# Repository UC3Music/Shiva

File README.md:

Shiva
--------------------------
Up to 8 piezo sensors with MIDI out (standard and USB) to make an electronic drumset

## v1.0 Prototype
### Known bugs

[Known bugs](https://github.com/UC3Music/Shiva/issues?q=is%3Aissue+is%3Aopen+label%3Abug)

## v0.1 Prototype
### PCBs

## Proof of concept

Proof of concept done with an Arduino Micro board (click on the images below to go to the videos):

# Acknowledgments

 * Inspired by KORG's [CLIPHIT](http://www.korg.com/us/products/drums/cliphit/)
 * Conditioning circuit for piezo sensors is based on [ScienceProg's circuit](http://www.scienceprog.com/thoughts-on-interfacing-piezo-vibration-sensor/)

# Credits
* Author: [David Estevez Fernandez](https://github.com/David-Estevez)

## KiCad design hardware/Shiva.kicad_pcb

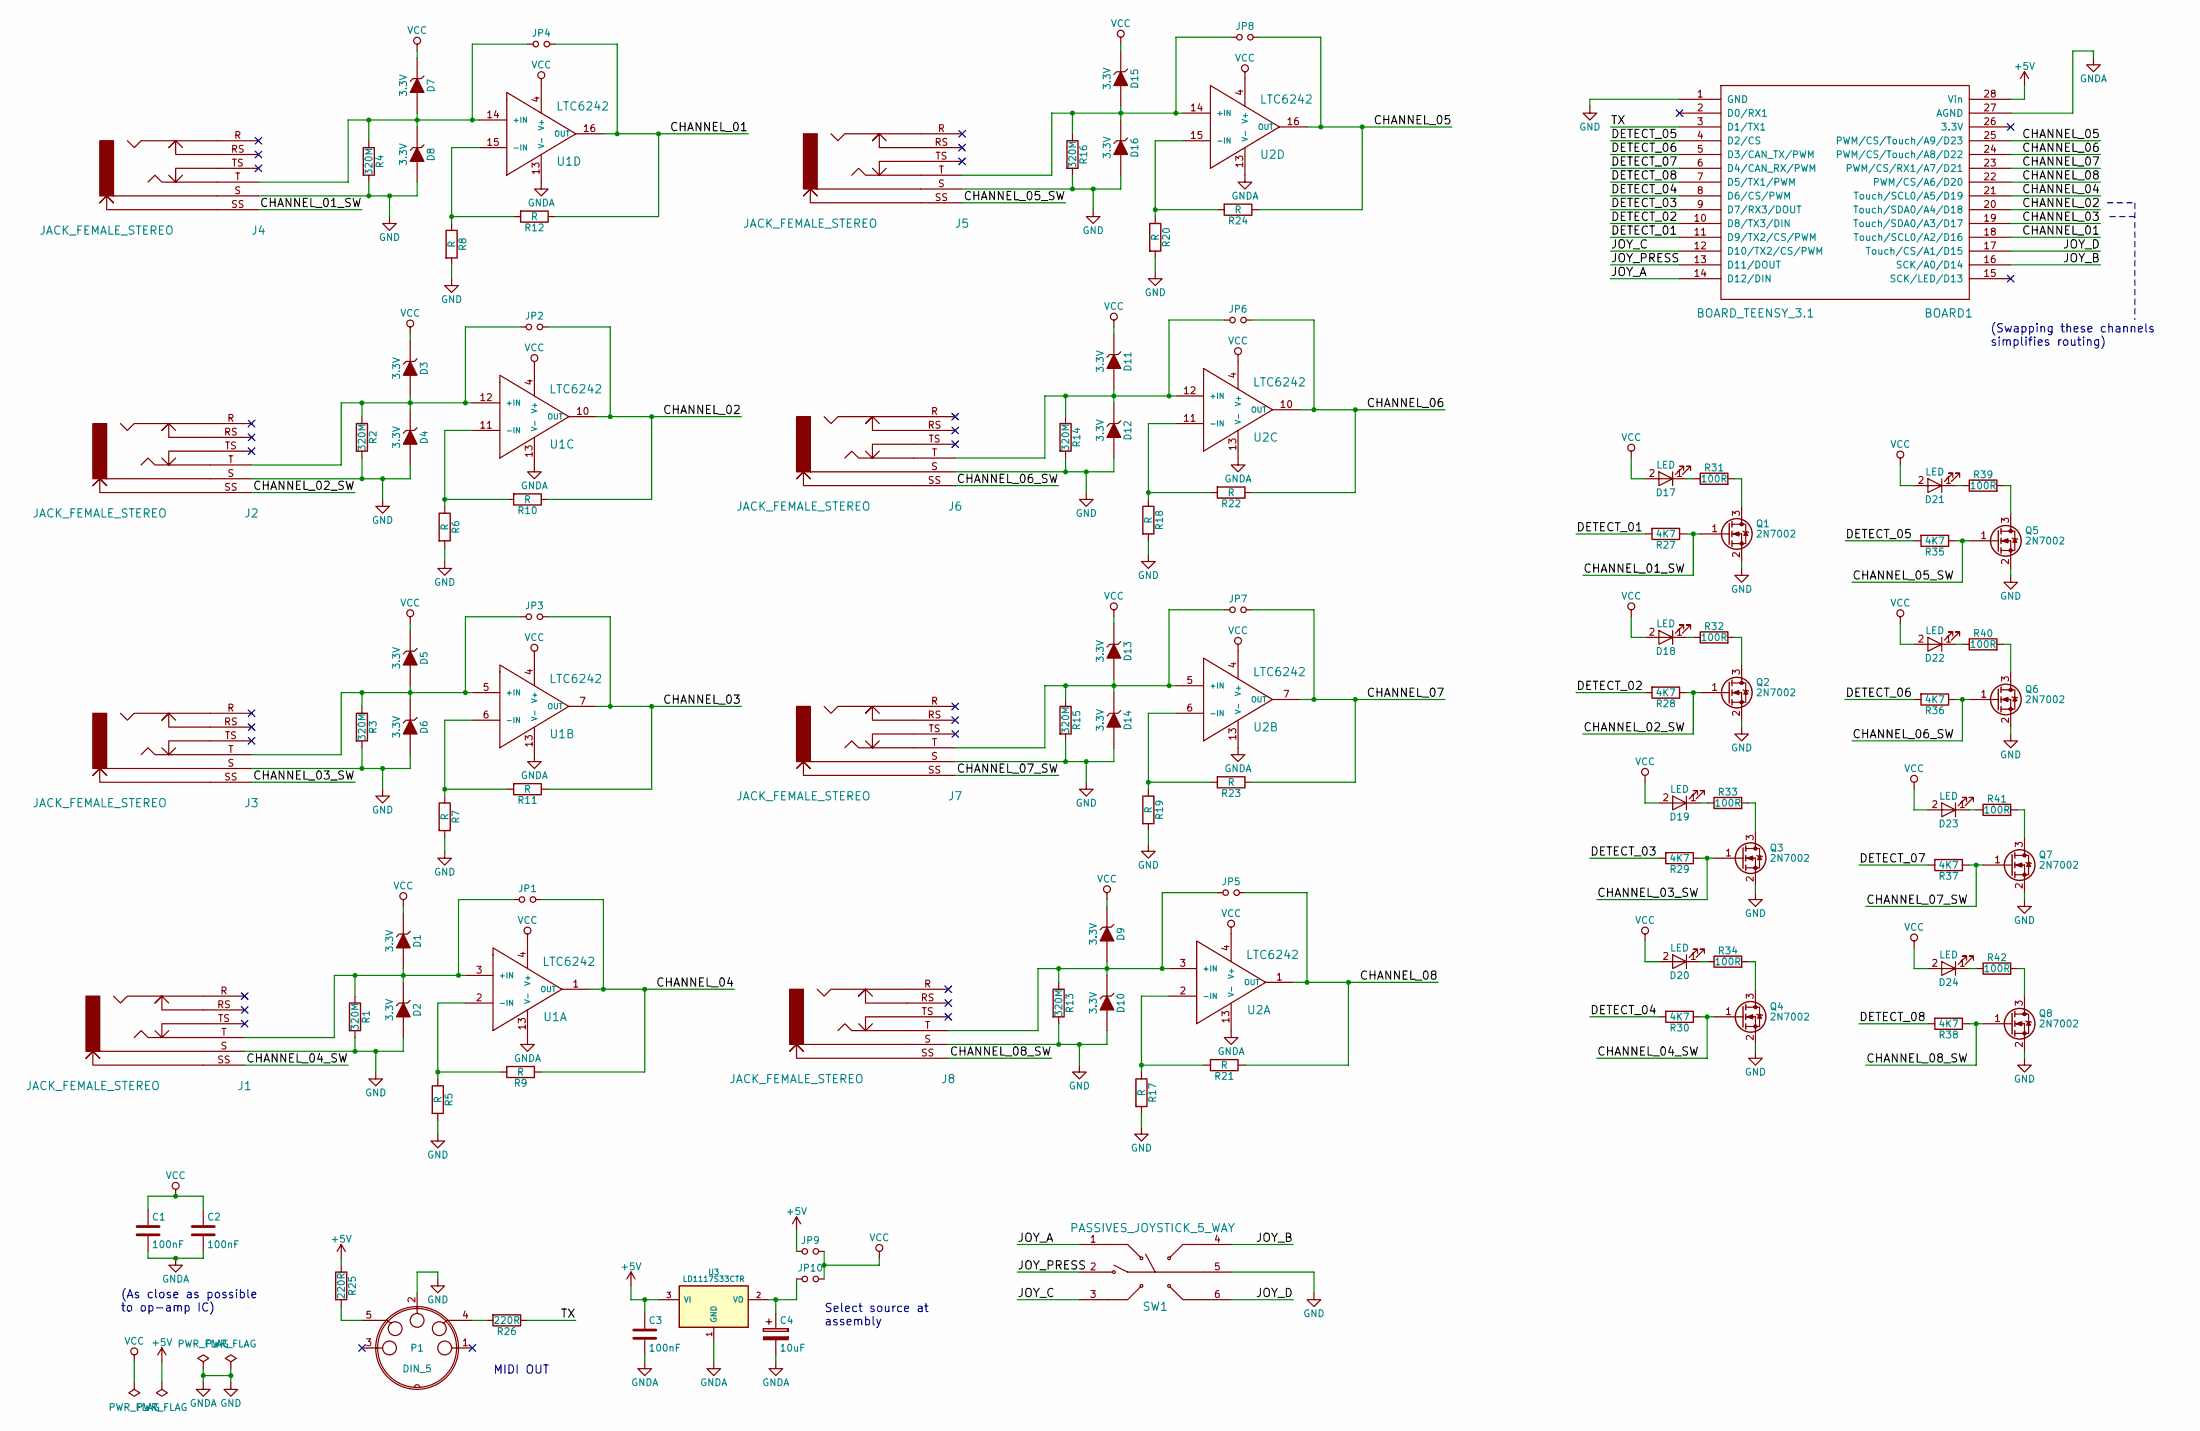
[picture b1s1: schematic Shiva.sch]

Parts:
BOARD1: BOARD_TEENSY_3.1; Board_Teensy_3_1
C1, C2, C3: 100nF; C_0805_HandSoldering
C4: 10uF; Package_1206_pol
D1, D2, D3, D4, D5, D6, D7, D8, D9, D10, D11, D12, D13, D14, D15, D16: 3.3V; D_SOD-323_HandSoldering
D17, D18, D19, D20, D21, D22, D23, D24: LED; LED_0805_HandSoldering
J1, J2, J3, J4, J5, J6, J7, J8: JACK_FEMALE_STEREO; CONN_Jack_Female_6.35mm_THD
JP1, JP2, JP3, JP4, JP5, JP6, JP7, JP8, JP9, JP10: Jumper_NO_Small; Miscellaneous_Solder_Jumper
P1: DIN_5; CONN_DIN5_Socket
Q1, Q2, Q3, Q4, Q5, Q6, Q7, Q8: 2N7002; SOT-23_Handsoldering
R1, R2, R3, R4, R13, R14, R15, R16: 320M; R_0805_HandSoldering
R5, R6, R7, R8, R9, R10, R11, R12, R17, R18, R19, R20, R21, R22, R23, R24: R; R_0805_HandSoldering
R25, R26: 220R; R_0805_HandSoldering
R27, R28, R29, R30, R35, R36, R37, R38: 4K7; R_0805_HandSoldering
R31, R32, R33, R34, R39, R40, R41, R42: 100R; R_0805_HandSoldering
SW1: PASSIVES_JOYSTICK_5_WAY; Switches_ALPS-SKRHAAE010
U1, U2: LTC6242; Package_SSOP16
U3: LD1117S33CTR; Package_SOT-223-3

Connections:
+5V: BOARD1.28 (Vin), C3.1, JP9.1, R25.1, U3.3 (VI)
/CHANNEL_01: BOARD1.18 (Touch/SCL0/A2/D16), JP4.2, R12.1, U1.16 (OUT)
/CHANNEL_01_SW: J4.SS, Q1.1 (G), R27.1
/CHANNEL_02: BOARD1.20 (Touch/SDA0/A4/D18), JP2.2, R10.1, U1.10 (OUT)
/CHANNEL_02_SW: J2.SS, Q2.1 (G), R28.1
/CHANNEL_03: BOARD1.19 (Touch/SDA0/A3/D17), JP3.2, R11.1, U1.7 (OUT)
/CHANNEL_03_SW: J3.SS, Q3.1 (G), R29.1
/CHANNEL_04: BOARD1.21 (Touch/SCL0/A5/D19), JP1.2, R9.1, U1.1 (OUT)
/CHANNEL_04_SW: J1.SS, Q4.1 (G), R30.1
/CHANNEL_05: BOARD1.25 (PWM/CS/Touch/A9/D23), JP8.2, R24.1, U2.16 (OUT)
/CHANNEL_05_SW: J5.SS, Q5.1 (G), R35.1
/CHANNEL_06: BOARD1.24 (PWM/CS/Touch/A8/D22), JP6.2, R22.1, U2.10 (OUT)
/CHANNEL_06_SW: J6.SS, Q6.1 (G), R36.1
/CHANNEL_07: BOARD1.23 (PWM/CS/RX1/A7/D21), JP7.2, R23.1, U2.7 (OUT)
/CHANNEL_07_SW: J7.SS, Q7.1 (G), R37.1
/CHANNEL_08: BOARD1.22 (PWM/CS/A6/D20), JP5.2, R21.1, U2.1 (OUT)
/CHANNEL_08_SW: J8.SS, Q8.1 (G), R38.1
/DETECT_01: BOARD1.11 (D9/TX2/CS/PWM), R27.2
/DETECT_02: BOARD1.10 (D8/TX3/DIN), R28.2
/DETECT_03: BOARD1.9 (D7/RX3/DOUT), R29.2
/DETECT_04: BOARD1.8 (D6/CS/PWM), R30.2
/DETECT_05: BOARD1.4 (D2/CS), R35.2
/DETECT_06: BOARD1.5 (D3/CAN_TX/PWM), R36.2
/DETECT_07: BOARD1.6 (D4/CAN_RX/PWM), R37.2
/DETECT_08: BOARD1.7 (D5/TX1/PWM), R38.2
/JOY_A: BOARD1.14 (D12/DIN), SW1.1
/JOY_B: BOARD1.16 (SCK/A0/D14), SW1.4
/JOY_C: BOARD1.12 (D10/TX2/CS/PWM), SW1.3
/JOY_D: BOARD1.17 (Touch/CS/A1/D15), SW1.6
/JOY_PRESS: BOARD1.13 (D11/DOUT), SW1.2
/TX: BOARD1.3 (D1/TX1), R26.1
GND: BOARD1.1 (GND), BOARD1.27 (AGND), C1.2, C2.2, C3.2, C4.2, D2.2 (A), D4.2 (A), D6.2 (A), D8.2 (A), D10.2 (A), D12.2 (A), D14.2 (A), D16.2 (A), J1.S, J2.S, J3.S, J4.S, J5.S, J6.S, J7.S, J8.S, P1.2, Q1.2 (S), Q2.2 (S), Q3.2 (S), Q4.2 (S), Q5.2 (S), Q6.2 (S), Q7.2 (S), Q8.2 (S), R1.2, R2.2, R3.2, R4.2, R5.2, R6.2, R7.2, R8.2, R13.2, R14.2, R15.2, R16.2, R17.2, R18.2, R19.2, R20.2, SW1.5, U1.13 (V-), U2.13 (V-), U3.1 (GND)
unnamed: C4.1, JP10.1, U3.2 (VO)
unnamed: D1.2 (A), D2.1 (K), J1.T, JP1.1, R1.1, U1.3 (+IN)
unnamed: D3.2 (A), D4.1 (K), J2.T, JP2.1, R2.1, U1.12 (+IN)
unnamed: D5.2 (A), D6.1 (K), J3.T, JP3.1, R3.1, U1.5 (+IN)
unnamed: D7.2 (A), D8.1 (K), J4.T, JP4.1, R4.1, U1.14 (+IN)
unnamed: D9.2 (A), D10.1 (K), J8.T, JP5.1, R13.1, U2.3 (+IN)
unnamed: D11.2 (A), D12.1 (K), J6.T, JP6.1, R14.1, U2.12 (+IN)
unnamed: D13.2 (A), D14.1 (K), J7.T, JP7.1, R15.1, U2.5 (+IN)
unnamed: D15.2 (A), D16.1 (K), J5.T, JP8.1, R16.1, U2.14 (+IN)
unnamed: D17.1 (K), R31.1
unnamed: D18.1 (K), R32.1
unnamed: D19.1 (K), R33.1
unnamed: D20.1 (K), R34.1
unnamed: D21.1 (K), R39.1
unnamed: D22.1 (K), R40.1
unnamed: D23.1 (K), R41.1
unnamed: D24.1 (K), R42.1
unnamed: P1.4, R26.2
unnamed: P1.5, R25.2
unnamed: Q1.3 (D), R31.2
unnamed: Q2.3 (D), R32.2
unnamed: Q3.3 (D), R33.2
unnamed: Q4.3 (D), R34.2
unnamed: Q5.3 (D), R39.2
unnamed: Q6.3 (D), R40.2
unnamed: Q7.3 (D), R41.2
unnamed: Q8.3 (D), R42.2
unnamed: R5.1, R9.2, U1.2 (-IN)
unnamed: R6.1, R10.2, U1.11 (-IN)
unnamed: R7.1, R11.2, U1.6 (-IN)
unnamed: R8.1, R12.2, U1.15 (-IN)
unnamed: R17.1, R21.2, U2.2 (-IN)
unnamed: R18.1, R22.2, U2.11 (-IN)
unnamed: R19.1, R23.2, U2.6 (-IN)
unnamed: R20.1, R24.2, U2.15 (-IN)
VCC: C1.1, C2.1, D1.1 (K), D3.1 (K), D5.1 (K), D7.1 (K), D9.1 (K), D11.1 (K), D13.1 (K), D15.1 (K), D17.2 (A), D18.2 (A), D19.2 (A), D20.2 (A), D21.2 (A), D22.2 (A), D23.2 (A), D24.2 (A), JP9.2, JP10.2, U1.4 (V+), U2.4 (V+)

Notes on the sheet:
MIDI OUT
Select source at assembly
(As close as possible to op-amp IC)
(Swapping these channels simplifies routing)

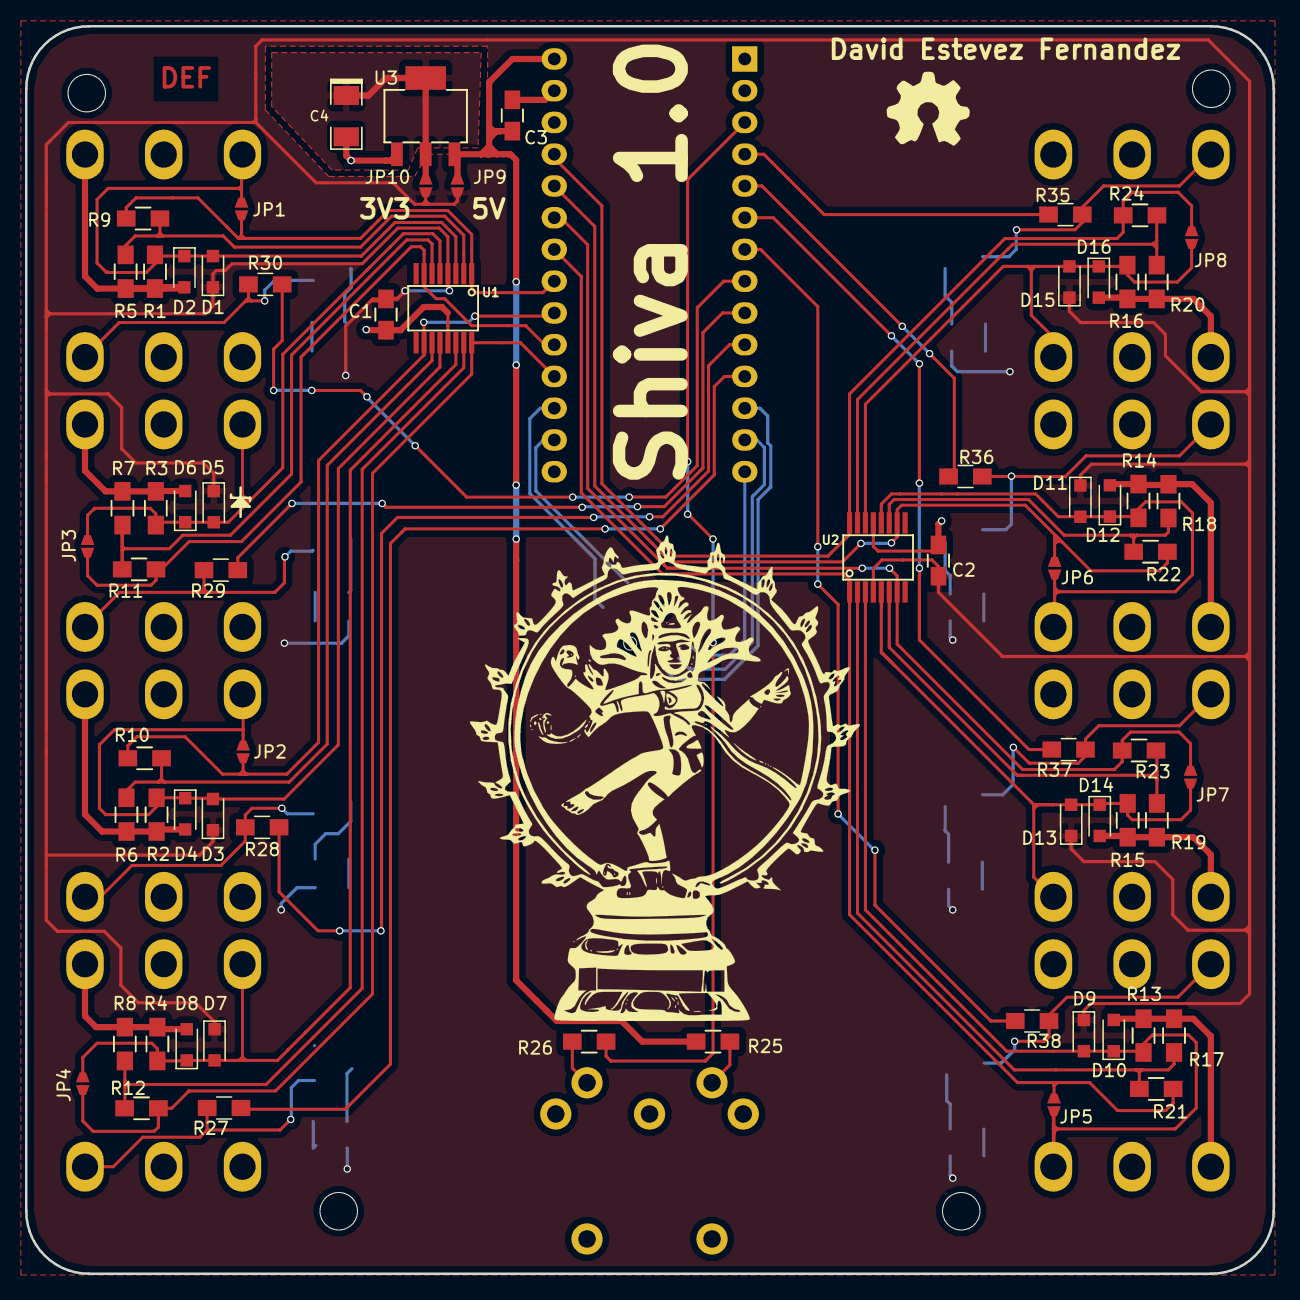
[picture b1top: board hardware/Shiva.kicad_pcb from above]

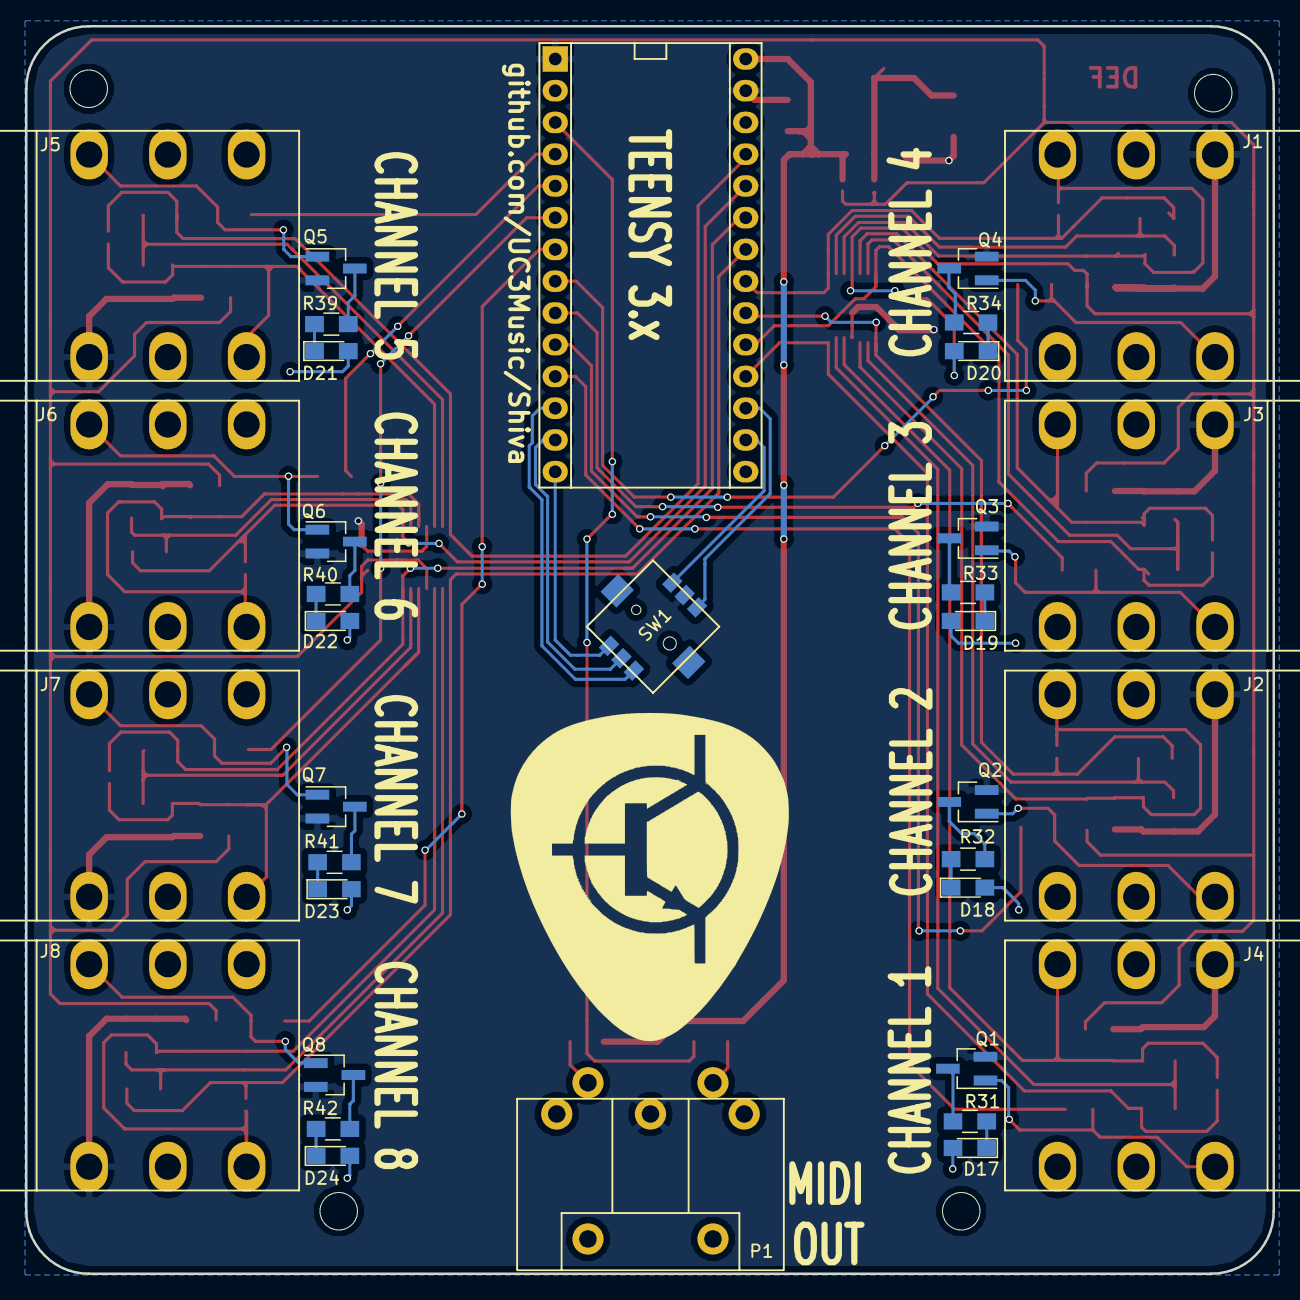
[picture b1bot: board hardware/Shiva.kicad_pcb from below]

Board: 2 copper layers, 99.8 x 99.8 mm, 106 parts (35 on the bottom side), 68 nets.

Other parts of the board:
Mechanical_drill_3mm, Mechanical_drill_3mm#2, Mechanical_drill_3mm#3, Mechanical_drill_3mm#4: Mechanical_Drill_3mm

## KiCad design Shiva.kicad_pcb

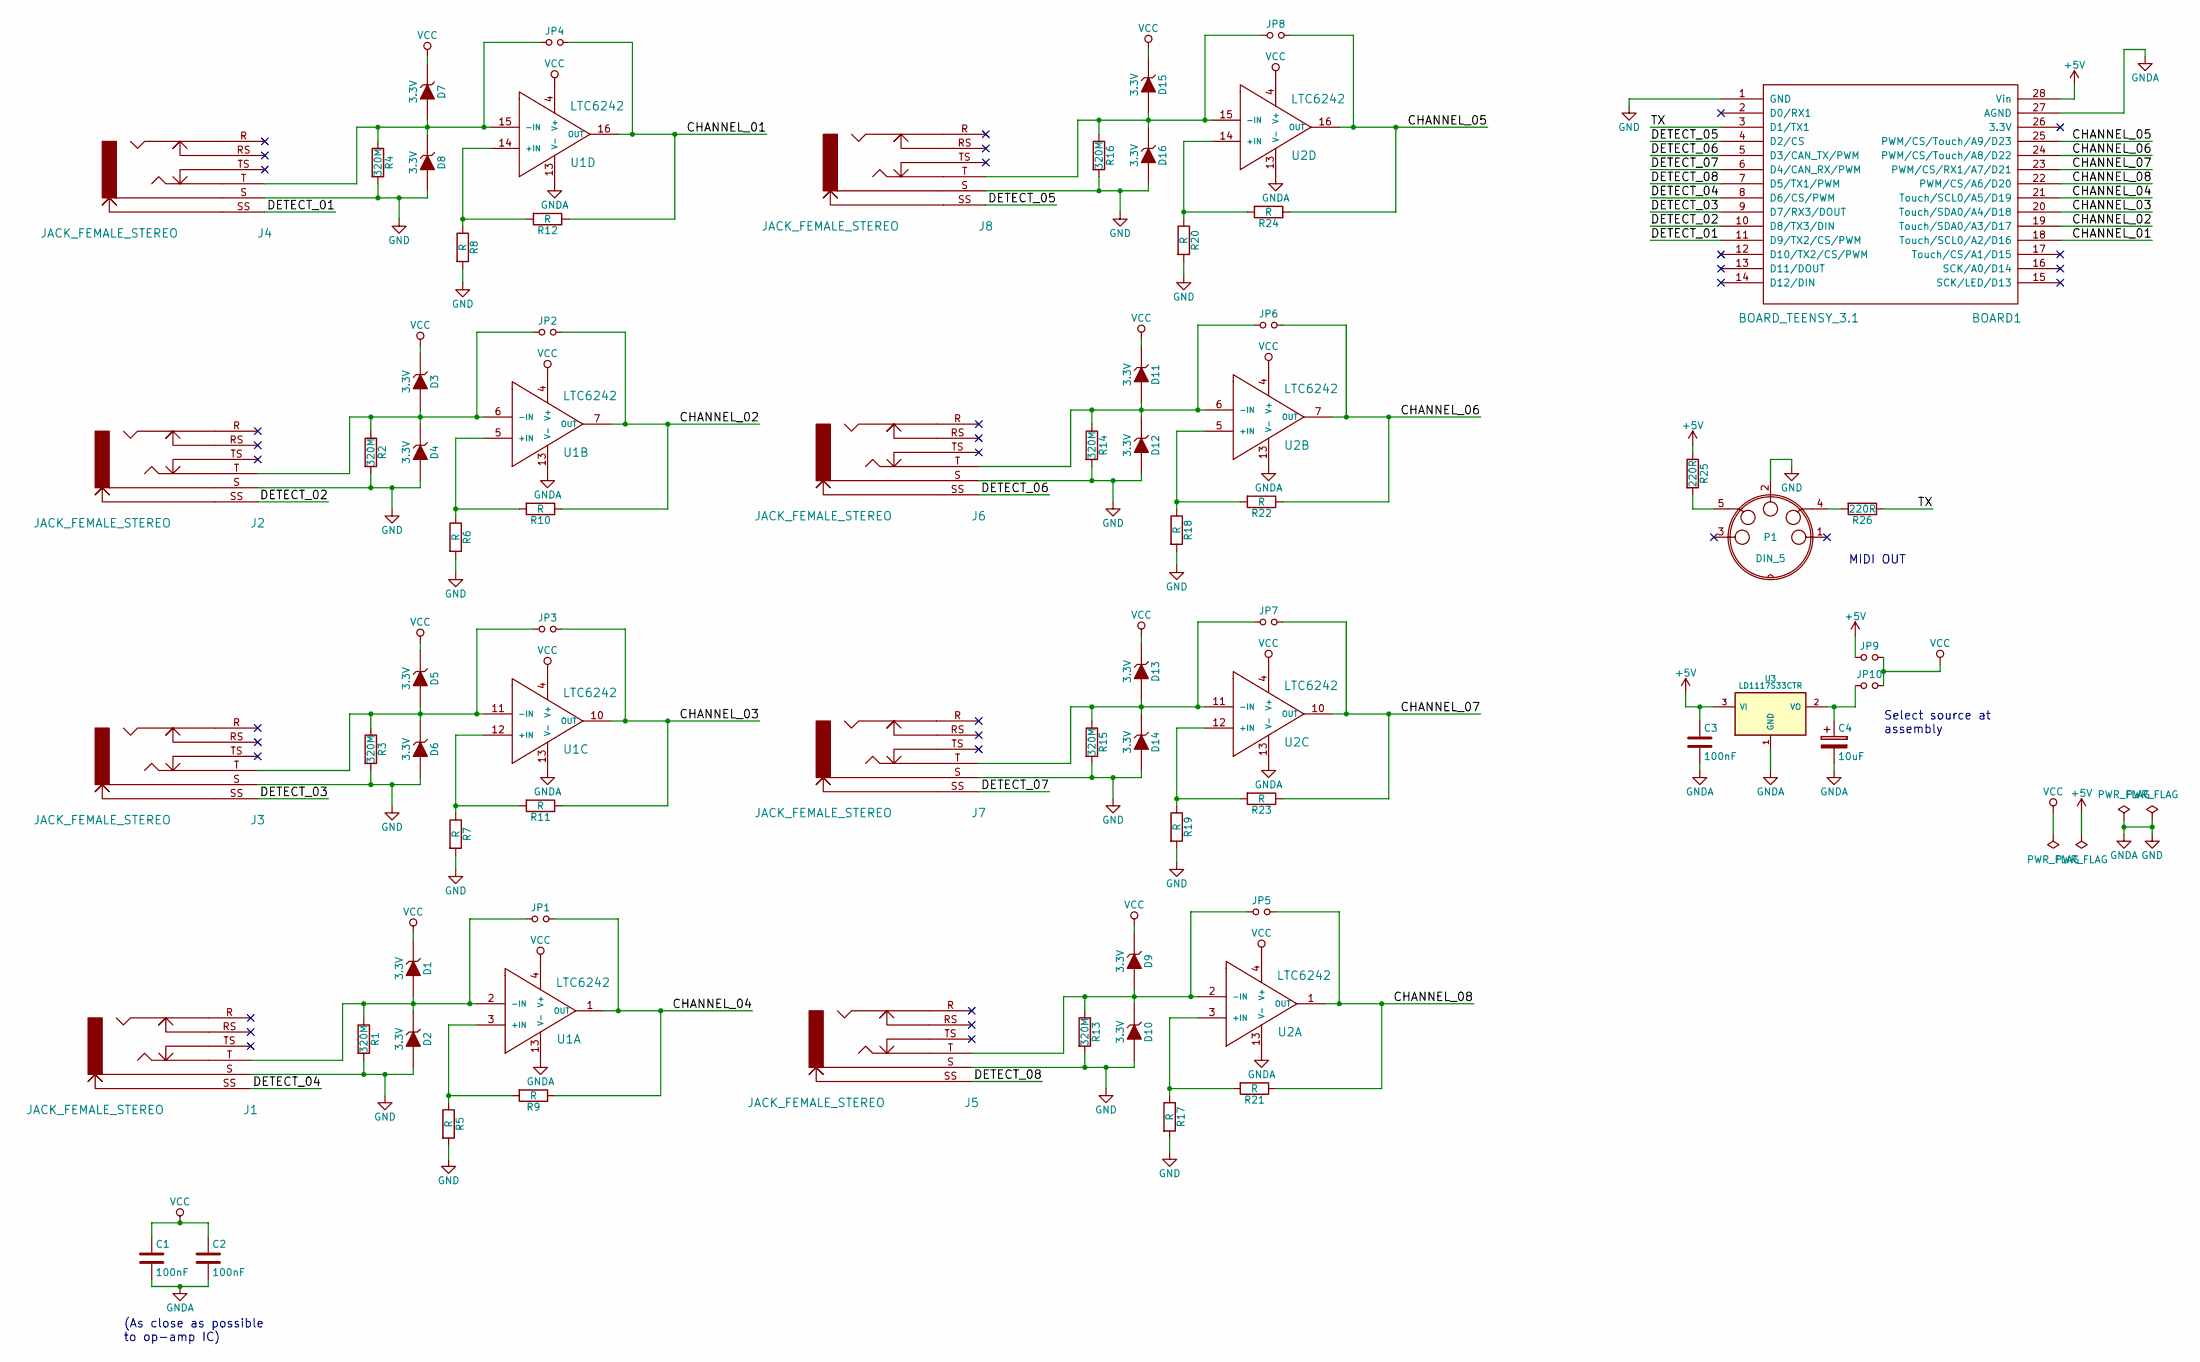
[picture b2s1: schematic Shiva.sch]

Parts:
BOARD1: BOARD_TEENSY_3.1; Board_Teensy_3_1
C1, C2, C3: 100nF; C_0805_HandSoldering
C4: 10uF; Package_1206_pol
D1, D2, D3, D4, D5, D6, D7, D8, D9, D10, D11, D12, D13, D14, D15, D16: 3.3V; SOD-323
J1, J2, J3, J4, J5, J6, J7, J8: JACK_FEMALE_STEREO; CONN_Jack_Female_6.35mm_THD
JP1, JP2, JP3, JP4, JP5, JP6, JP7, JP8, JP9, JP10: Jumper_NO_Small; Miscellaneous_Solder_Jumper
P1: DIN_5; CONN_DIN5_Socket
R1, R2, R3, R4, R13, R14, R15, R16: 320M; R_0805_HandSoldering
R5, R6, R7, R8, R9, R10, R11, R12, R17, R18, R19, R20, R21, R22, R23, R24: R; R_0603_HandSoldering
R25, R26: 220R; R_0603_HandSoldering
U1, U2: LTC6242; Package_SSOP16
U3: LD1117S33CTR; Package_SOT-223-3

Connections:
+5V: BOARD1.28 (Vin), C3.1, JP9.1, R25.1, U3.3 (VI)
/CHANNEL_01: BOARD1.18 (Touch/SCL0/A2/D16), JP4.2, R12.1, U1.16 (OUT)
/CHANNEL_02: BOARD1.19 (Touch/SDA0/A3/D17), JP2.2, R10.1, U1.7 (OUT)
/CHANNEL_03: BOARD1.20 (Touch/SDA0/A4/D18), JP3.2, R11.1, U1.10 (OUT)
/CHANNEL_04: BOARD1.21 (Touch/SCL0/A5/D19), JP1.2, R9.1, U1.1 (OUT)
/CHANNEL_05: BOARD1.25 (PWM/CS/Touch/A9/D23), JP8.2, R24.1, U2.16 (OUT)
/CHANNEL_06: BOARD1.24 (PWM/CS/Touch/A8/D22), JP6.2, R22.1, U2.7 (OUT)
/CHANNEL_07: BOARD1.23 (PWM/CS/RX1/A7/D21), JP7.2, R23.1, U2.10 (OUT)
/CHANNEL_08: BOARD1.22 (PWM/CS/A6/D20), JP5.2, R21.1, U2.1 (OUT)
/DETECT_01: BOARD1.11 (D9/TX2/CS/PWM), J4.SS
/DETECT_02: BOARD1.10 (D8/TX3/DIN), J2.SS
/DETECT_03: BOARD1.9 (D7/RX3/DOUT), J3.SS
/DETECT_04: BOARD1.8 (D6/CS/PWM), J1.SS
/DETECT_05: BOARD1.4 (D2/CS), J8.SS
/DETECT_06: BOARD1.5 (D3/CAN_TX/PWM), J6.SS
/DETECT_07: BOARD1.6 (D4/CAN_RX/PWM), J7.SS
/DETECT_08: BOARD1.7 (D5/TX1/PWM), J5.SS
/TX: BOARD1.3 (D1/TX1), R26.1
GND: BOARD1.1 (GND), BOARD1.27 (AGND), C1.2, C2.2, C3.2, C4.2, D2.2 (A), D4.2 (A), D6.2 (A), D8.2 (A), D10.2 (A), D12.2 (A), D14.2 (A), D16.2 (A), J1.S, J2.S, J3.S, J4.S, J5.S, J6.S, J7.S, J8.S, P1.2, R1.2, R2.2, R3.2, R4.2, R5.2, R6.2, R7.2, R8.2, R13.2, R14.2, R15.2, R16.2, R17.2, R18.2, R19.2, R20.2, U1.13 (V-), U2.13 (V-), U3.1 (GND)
unnamed: C4.1, JP10.1, U3.2 (VO)
unnamed: D1.2 (A), D2.1 (K), J1.T, JP1.1, R1.1, U1.2 (-IN)
unnamed: D3.2 (A), D4.1 (K), J2.T, JP2.1, R2.1, U1.6 (-IN)
unnamed: D5.2 (A), D6.1 (K), J3.T, JP3.1, R3.1, U1.11 (-IN)
unnamed: D7.2 (A), D8.1 (K), J4.T, JP4.1, R4.1, U1.15 (-IN)
unnamed: D9.2 (A), D10.1 (K), J5.T, JP5.1, R13.1, U2.2 (-IN)
unnamed: D11.2 (A), D12.1 (K), J6.T, JP6.1, R14.1, U2.6 (-IN)
unnamed: D13.2 (A), D14.1 (K), J7.T, JP7.1, R15.1, U2.11 (-IN)
unnamed: D15.2 (A), D16.1 (K), J8.T, JP8.1, R16.1, U2.15 (-IN)
unnamed: P1.4, R26.2
unnamed: P1.5, R25.2
unnamed: R5.1, R9.2, U1.3 (+IN)
unnamed: R6.1, R10.2, U1.5 (+IN)
unnamed: R7.1, R11.2, U1.12 (+IN)
unnamed: R8.1, R12.2, U1.14 (+IN)
unnamed: R17.1, R21.2, U2.3 (+IN)
unnamed: R18.1, R22.2, U2.5 (+IN)
unnamed: R19.1, R23.2, U2.12 (+IN)
unnamed: R20.1, R24.2, U2.14 (+IN)
VCC: C1.1, C2.1, D1.1 (K), D3.1 (K), D5.1 (K), D7.1 (K), D9.1 (K), D11.1 (K), D13.1 (K), D15.1 (K), JP9.2, JP10.2, U1.4 (V+), U2.4 (V+)

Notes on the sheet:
MIDI OUT
Select source at assembly
(As close as possible to op-amp IC)

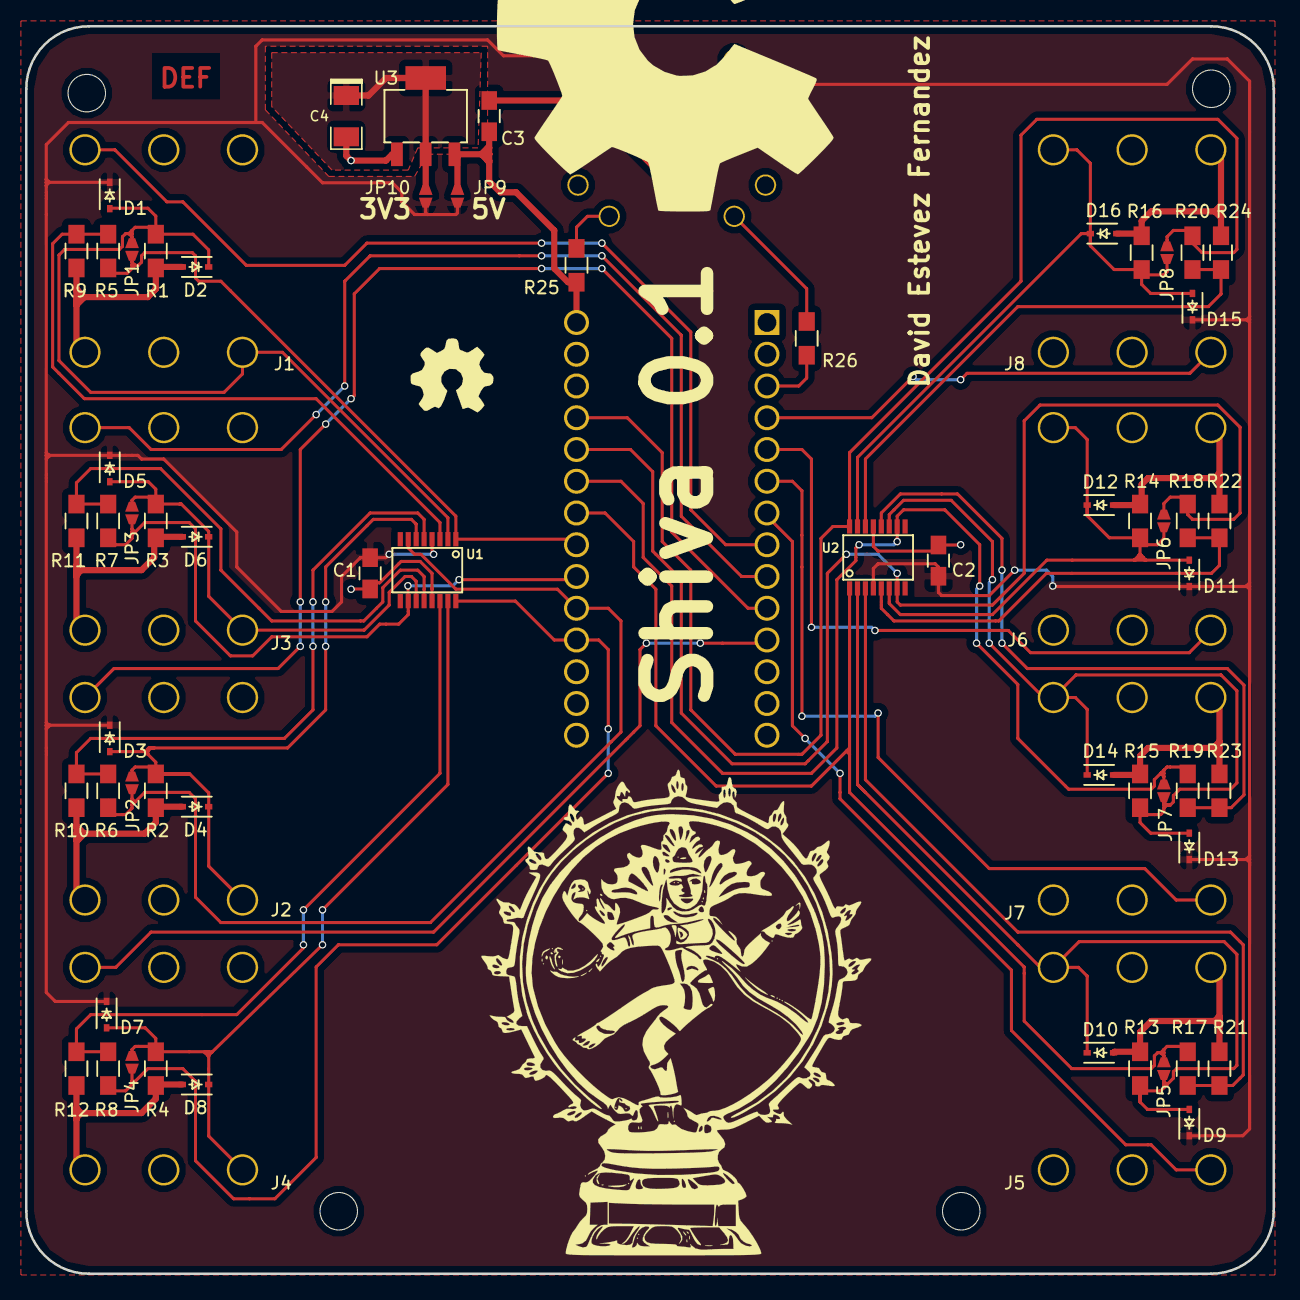
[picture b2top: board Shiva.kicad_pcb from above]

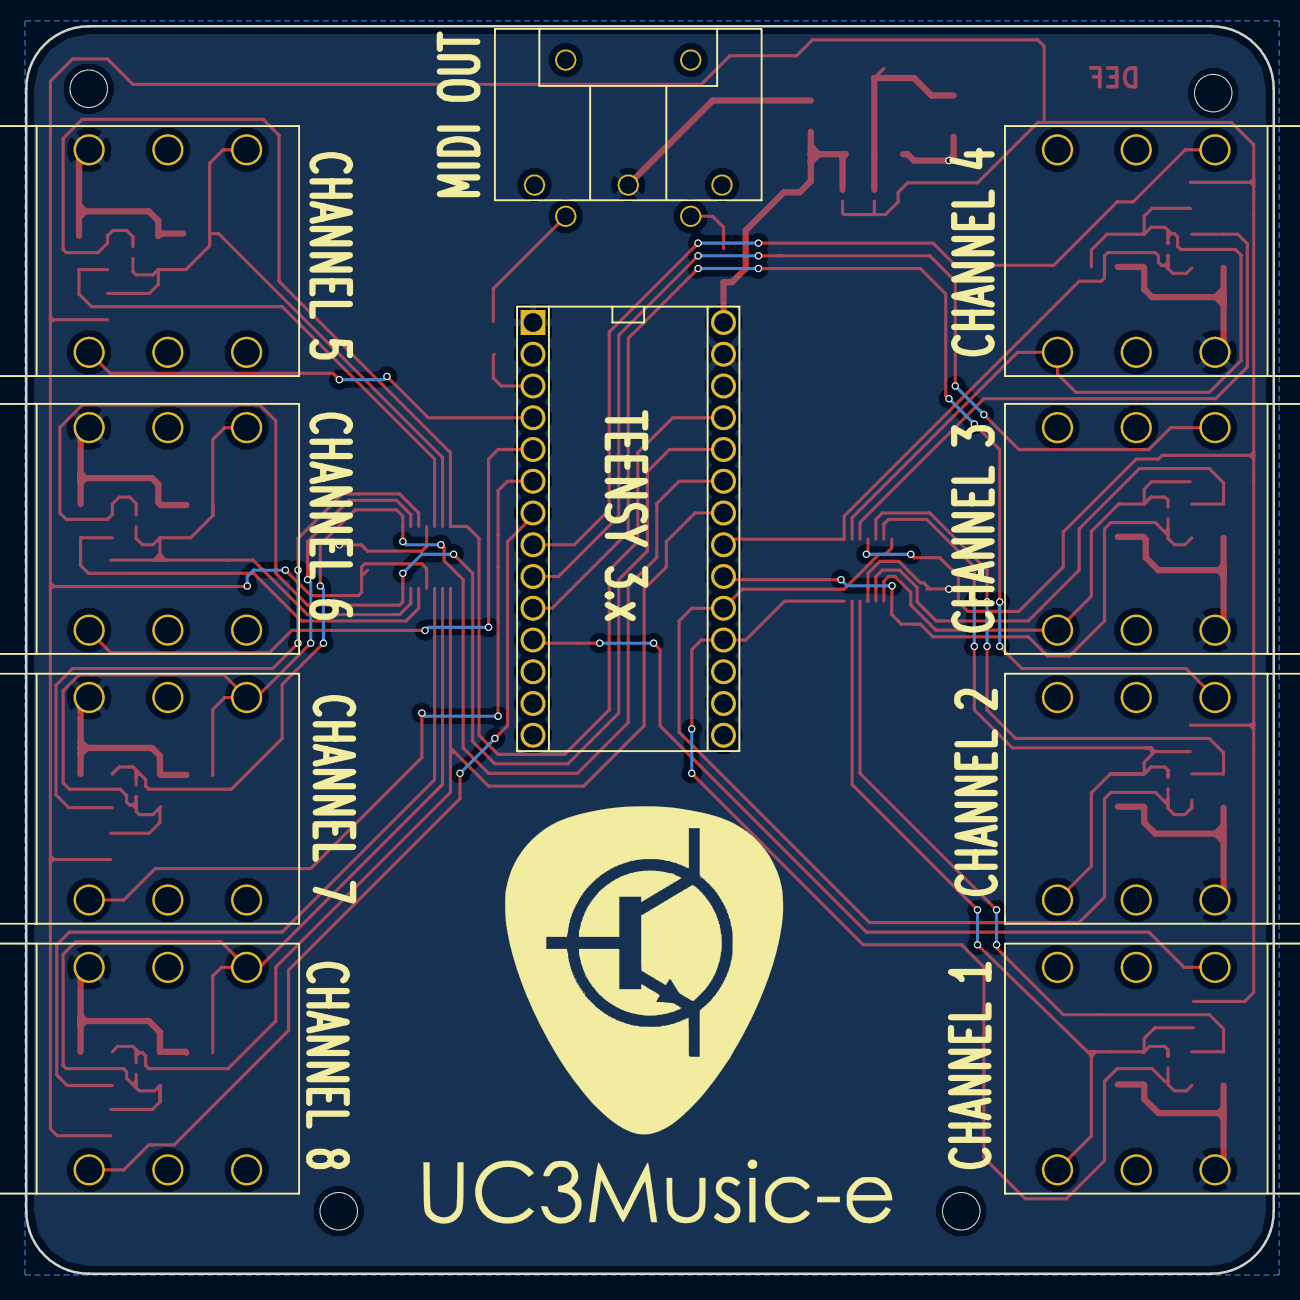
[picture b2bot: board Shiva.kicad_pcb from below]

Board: 2 copper layers, 99.8 x 99.8 mm, 73 parts (10 on the bottom side), 39 nets.

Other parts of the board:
Mechanical_drill_3mm, Mechanical_drill_3mm#2, Mechanical_drill_3mm#3, Mechanical_drill_3mm#4: Mechanical_Drill_3mm

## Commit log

2015-10-16 Start designing input conditioning circuit
2015-10-16 Add gitignore for bak files
2015-10-18 Add 8 input channels, Teensy, start MIDI interface
2015-10-19 Add MIDI and regulator
2015-10-19 Generate netlist
2015-10-19 Add some cmp assignments
2015-10-20 Assign SSOP16 footprint
2015-10-20 Assign 1206 pol to footprints
2015-10-22 Preliminary routing
2015-10-22 Add logos, copper front plane
2015-10-23 Add drills and heatsinking
2015-10-23 Fix bug with midi tx. Finish silkscreen
2015-10-23 Add readme
2015-10-23 Modify silkscreen
2015-10-27 Fixed solder jumpers
2015-10-27 Generate GERBER files
2015-10-30 Move hardware files to hardware folder
2015-10-30 Add Arduino test MIDI firmware
2015-10-30 Add things to README
2015-10-30 Add videos to README
2015-10-30 Workaround for video links not working
2015-10-30 Add explanation for video thumbnails
2015-11-04 Add BOM file
2015-11-07 Add pictures of prototype
2015-11-07 Add PCB images to README
2015-11-08 Change footprint for Teensy
2015-11-11 Add Acknowledgements to README.md
2015-11-16 Add datasheets to docs
2015-12-10 Firmware for hardware testing of Shiva prototype
2016-09-26 Rewrite code to allow 8 channels
2016-09-27 Add serial commands to enable channel feedback
2016-09-27 Add support to edit notes via serial port
2016-09-27 Add support for threshold adjustment
2016-09-29 Add basic python serial interface
2016-09-29 Add basic connection GUI for Shiva
2016-09-29 Add support to edit channels in GUI (not connected to backend
2016-09-29 Add connection with Shiva backend to send configuration commands
2016-10-01 Add support to get current status in Shiva firmware
2016-10-01 Add support to get current channel status in Shiva firmware
2016-10-06 Add test code to implement threaded reader of serial port
2016-10-08 Modify communication protocol to show command number on verbose mode
2016-10-08 Add class LevelFeedbackReader to read information from Shiva's verbose mode
2016-10-08 Make BasicLevelFeedbackReader available for import
2016-10-08 Integrate LevelFeedbackLReader into Shiva CLI
2016-10-08 Fix small bugs in feedback mechanism
2016-10-08 Add support for feedback on a single channel
2016-10-08 Fix issue #8
2016-10-09 Fix signals to work on all channels (feedback enabled on all channels)
2018-03-04 Fix swapped op-amp inputs
2018-03-04 Fix jacks, thin pads, swapped silkscreen
2018-03-04 Add repo url
2018-03-04 Fix SMD footprints too small
2018-03-07 Change placement of required components
2018-03-08 Reroute channel 4
2018-03-13 Route channel 3
2018-03-13 Route channel 2
2018-03-14 Document channel swap in schematic
2018-03-14 Restore old zones (fixes #12)
2018-03-15 Route channel 1
2018-03-15 Route channel 5, swap channels to simplify op-amp routing
2018-03-15 Route channel 6
2018-03-15 Route channel 7
2018-03-15 Route channel 8
2018-03-15 Fill zones, connect remaining stuff, beautify tracks
2018-03-21 Add more LEDs to schematic
2018-03-21 Fix labels for connections to new LEDs
2018-03-21 Assign footprints for new LED-related components
2018-03-22 Route LED for channel 1
2018-03-22 Add reference lines, move text on silkscreen
2018-03-22 Reload footprints
2018-03-22 Add KEDs for channels 2-8
2018-03-23 Fix some tracks to make them much more better
2018-03-24 Add 5-way joystick as user interface
2018-04-15 Add new GERBER files
2018-04-15 Add last minute fixes
2018-04-24 Add new components to BOM
2018-06-11 Add lights test
2018-08-19 Add sensor detection
    Fixes #18
2018-08-20 Enable on/off/blinking LEDs
    Due to hardware limitations (well, library limitations would be more
    precise) only one LED can blink at a time. Still, we can work with
    just that for now.
2018-08-20 Enable reading buttons
2018-08-21 Refactor firmware, add detect rates
2018-08-21 Add support to query info from board
2018-08-21 Add periodic update of GUI
2018-08-21 Enable sensor detection
2018-08-23 Add getting in and out of menu
2018-08-23 Add selecting different channels in menu
2018-08-23 Fix bug with reverse travelling channels
2018-08-23 Add drum type selection using joystick
    Fixes #19
2018-08-23 Send MIDI notes out of the MIDI out connector
2018-08-23 Fix channel order, adjust thresholds for channels not being used
2018-08-23 Fix MIDI out not working (not initialized)
